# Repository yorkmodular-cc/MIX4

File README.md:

# York Modular 4-channel Eurorack mixer

**This module is now discontinued - there will be no more made unless there is sufficient demand to justify a new run of boards and panels.**

[![CC BY-SA 4.0][cc-by-sa-shield]][cc-by-sa]

This work is licensed under a
[Creative Commons Attribution-ShareAlike 4.0 International License][cc-by-sa].

[![CC BY-SA 4.0][cc-by-sa-image]][cc-by-sa]

[cc-by-sa]: http://creativecommons.org/licenses/by-sa/4.0/
[cc-by-sa-image]: https://licensebuttons.net/l/by-sa/4.0/88x31.png
[cc-by-sa-shield]: https://img.shields.io/badge/License-CC%20BY--SA%204.0-lightgrey.svg

What you'll find here:

- `gerbers` - the Gerber files are in here; if you want to fabricate your own run of boards, these are what the fab will need.
- `4ch-euromixer-BOM.xlsx` - bill of materials
- `4ch-euromixer.png` - circuit schematic for reference
- `4ch-euromixer.{dxf,fpd}` - panel files in AutoCAD format (`.dxf`) and Front Panel Designer format (`.fpd`). These are _blank_ panels.
- `4ch-euromixer-lettered.{dxf,fpd}` - as above, but appropriately lettered.
- `4ch-euromixer.stl` - OpenSCAD `.stl` file for 3D printing. Depending on the accuracy of your 3D printer, you may need to take a deburring tool to the jack and pot holes in order to get things to fit.
- `mix4-mainboard.kicad_pcb` - KiCAD board file for mainboard.
- `mix4-panel.kicad_pcb` - KiCAD board file for front panel.

If you're planning to have panels laser-cut then the DXF files are probably what you want - if your fabricator requires Adobe Illustrator or a similar format 
then importing the DXF files into a package such as Inkscape and then re-exporting them as SVG should do the trick.

If you're planning to 3D-print a panel, just pull the STL file into your package of choice (I use Cura, others are available) and tweak the settings to suit.
My own experience is that printing with PLA at 200C with a heated bed (60-70C) gives good results - whether you use a raft is a matter of personal choice; for
large panels I tend to use a 10mm raft, even on a heated bed. You don't need insanely high resolution either - 0.2mm/layer is plenty good enough and print time
is around 3hrs on my AnyCubic i3.

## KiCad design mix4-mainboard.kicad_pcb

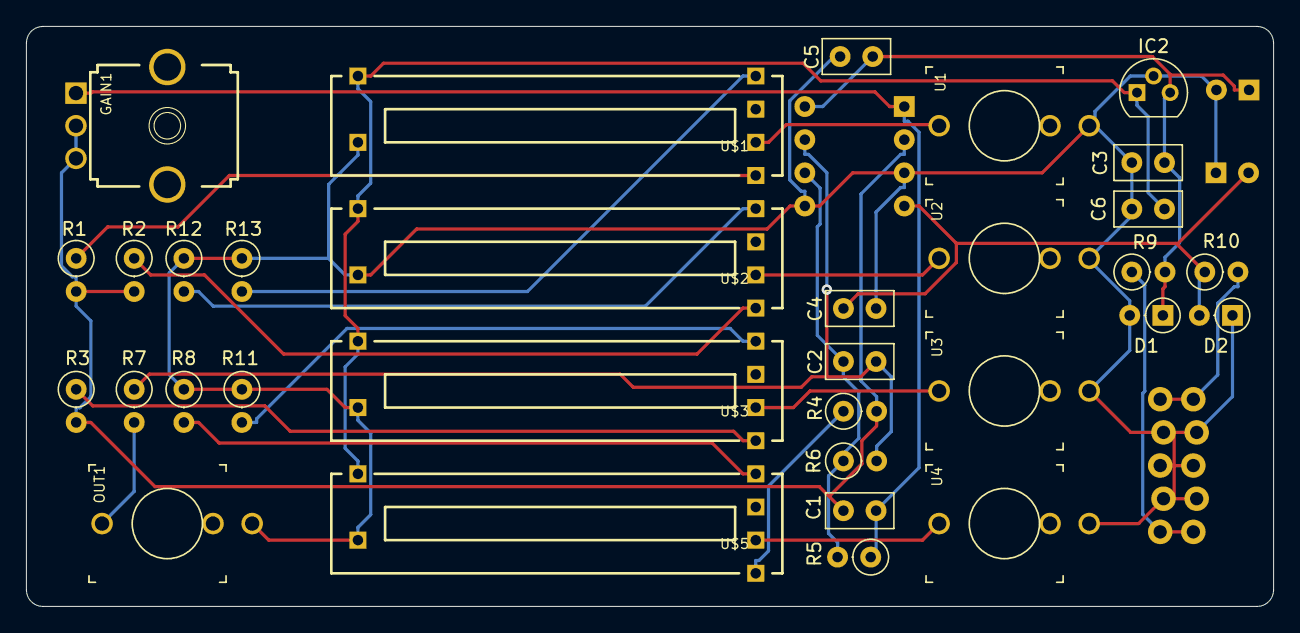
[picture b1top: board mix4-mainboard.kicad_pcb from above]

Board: 2 copper layers, 95.6 x 44.4 mm, 36 parts (0 on the bottom side), 23 nets.

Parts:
C1, C2: 47p; C_Disc_D5.0mm_W2.5mm_P2.50mm
C3, C4, C5, C6: 100n; C_Disc_D5.0mm_W2.5mm_P2.50mm
C7, C8: CP; CP_Radial_D5.0mm_P2.50mm
D1, D2: D; D_DO-35_SOD27_P2.54mm_Vertical_AnodeUp
GAIN1: 1M; 9MM_SNAP-IN_POT
IC1: TL072P; DIP-8_W7.62mm_Socket
IC2: 78Z; TO-92
LOCK1: EURO_POWER_LOCK; EURO_PWR_HEADER_LOCK
OUT1: THONKICONNNEW; WQP-PJ301M-12_JACK
R1, R2, R3, R4: 100k; R_Axial_DIN0207_L6.3mm_D2.5mm_P2.54mm_Vertical
R5, R6, R7, R8, R11, R12, R13: 1k; R_Axial_DIN0207_L6.3mm_D2.5mm_P2.54mm_Vertical
R9, R10: 22R; R_Axial_DIN0207_L6.3mm_D2.5mm_P2.54mm_Vertical
U1, U2, U3, U4: THONKICONNNEW; WQP-PJ301M-12_JACK
U$1, U$2, U$3, U$5: 50k; ALPHA_ILL_FADER_20MM

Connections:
+5V: C6.2, IC2.1, U$1.B, U$2.B, U$3.B, U$5.B
GND: C3.1, C4.2, C5.1, C6.1, C7.2, C8.1, D1.2, D2.1, IC1.3, IC1.5, IC2.2, LOCK1.GND1, LOCK1.GND2, LOCK1.GND3, LOCK1.GND4, LOCK1.GND5, LOCK1.GND6, OUT1.P$3_SLEEVE, R8.1, R11.1, R12.1, R13.1, U1.P$3_SLEEVE, U2.P$3_SLEEVE, U3.P$3_SLEEVE, U4.P$3_SLEEVE, U$1.3, U$2.3, U$3.3, U$5.3
unnamed: C1.1, GAIN1.2, GAIN1.3, IC1.2, R1.2, R2.2, R3.2, R4.2
unnamed: C1.2, GAIN1.1, IC1.1, R5.1
unnamed: C2.1, IC1.6, R5.2, R6.1
unnamed: C2.2, IC1.7, R6.2, R7.1
unnamed: LOCK1.NEG1, LOCK1.NEG2, R10.2
unnamed: LOCK1.POS1, LOCK1.POS2, R9.1
unnamed: OUT1.P$1_TIP, R7.2
unnamed: R1.1, U$1.2
unnamed: R2.1, U$2.2
unnamed: R3.1, U$3.2
unnamed: R4.1, U$5.2
unnamed: R8.2, U$5.E
unnamed: R11.2, U$3.E
unnamed: R12.2, U$2.E
unnamed: R13.2, U$1.E
unnamed: U1.P$1_TIP, U$1.1
unnamed: U2.P$1_TIP, U$2.1
unnamed: U3.P$1_TIP, U$3.1
unnamed: U4.P$1_TIP, U$5.1
V+: C3.2, C5.2, C7.1, D1.1, IC1.8, IC2.3, R9.2
V-: C4.1, C8.2, D2.2, IC1.4, R10.1

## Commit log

2019-02-06 Added panel files and updated readme
2019-02-06 README.md edited online with Bitbucket
2019-02-09 Fix broken PNG file
2019-02-09 Add values to faders
2021-04-17 Update README file
2021-04-17 Added Gerber files
2022-05-13 Add files via upload
    Add KiCAD board files for mainboard and front panel
2022-05-13 Create LICENSE
